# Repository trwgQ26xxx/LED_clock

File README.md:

# LED clock with thermometer

Clock with DS3231/DS3231M RTC.

# Disclaimer

I do not consent to the use of all or part of the project for commercial purposes!

Nie wyrażam zgody na wykorzystanie całości bądź części projektu w celach zarobkowych!

# License

Shield: [![CC BY-NC-SA 4.0][cc-by-nc-sa-shield]][cc-by-nc-sa]

This work is licensed under a
[Creative Commons Attribution-NonCommercial-ShareAlike 4.0 International License][cc-by-nc-sa].

[![CC BY-NC-SA 4.0][cc-by-nc-sa-image]][cc-by-nc-sa]

[cc-by-nc-sa]: http://creativecommons.org/licenses/by-nc-sa/4.0/
[cc-by-nc-sa-image]: https://licensebuttons.net/l/by-nc-sa/4.0/88x31.png
[cc-by-nc-sa-shield]: https://img.shields.io/badge/License-CC%20BY--NC--SA%204.0-lightgrey.svg

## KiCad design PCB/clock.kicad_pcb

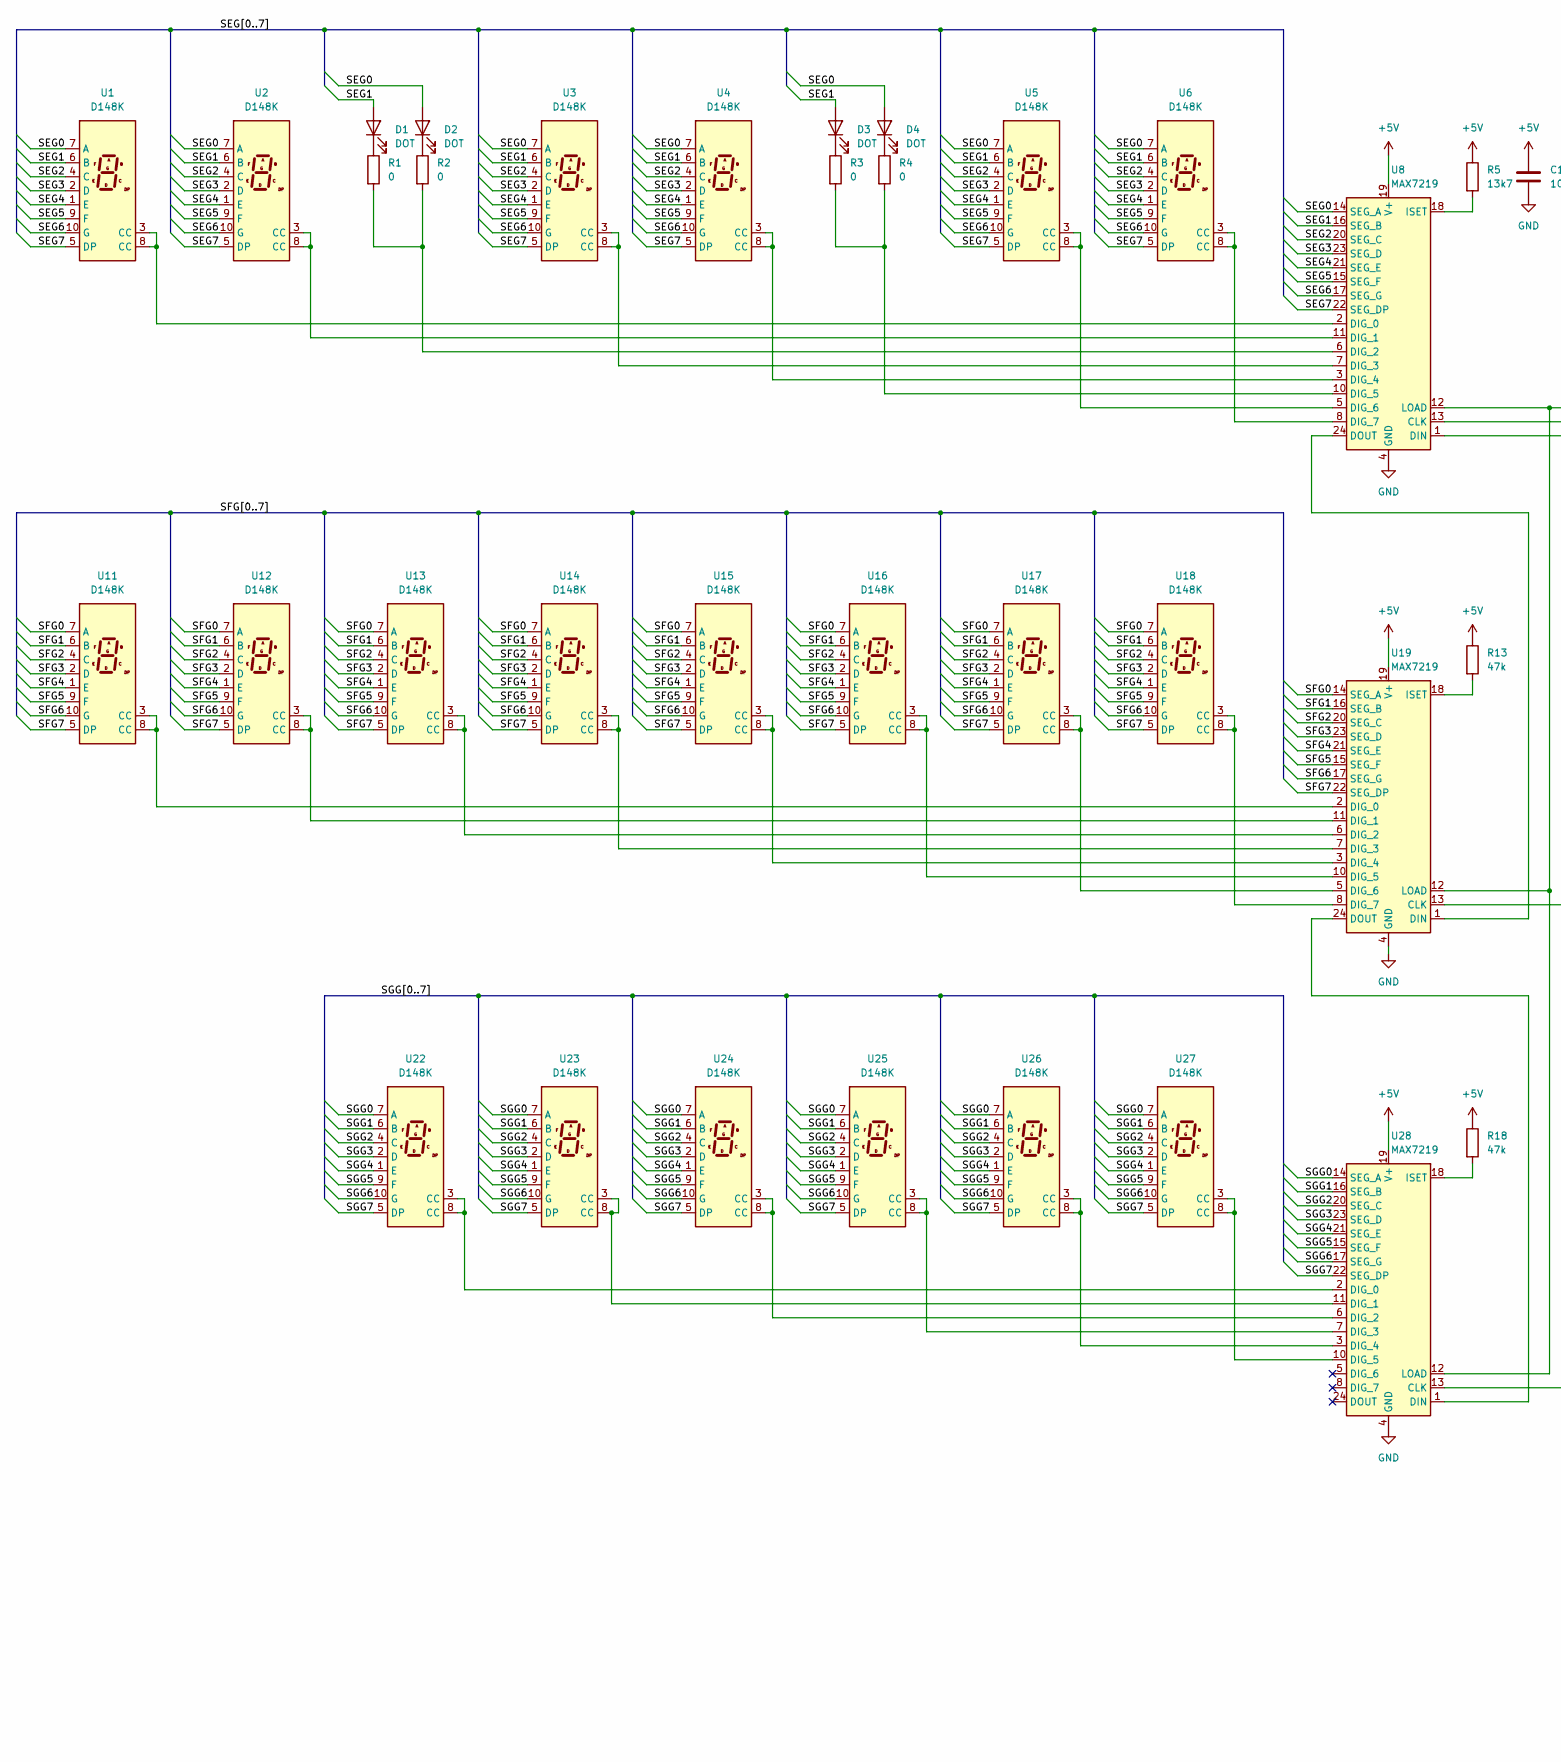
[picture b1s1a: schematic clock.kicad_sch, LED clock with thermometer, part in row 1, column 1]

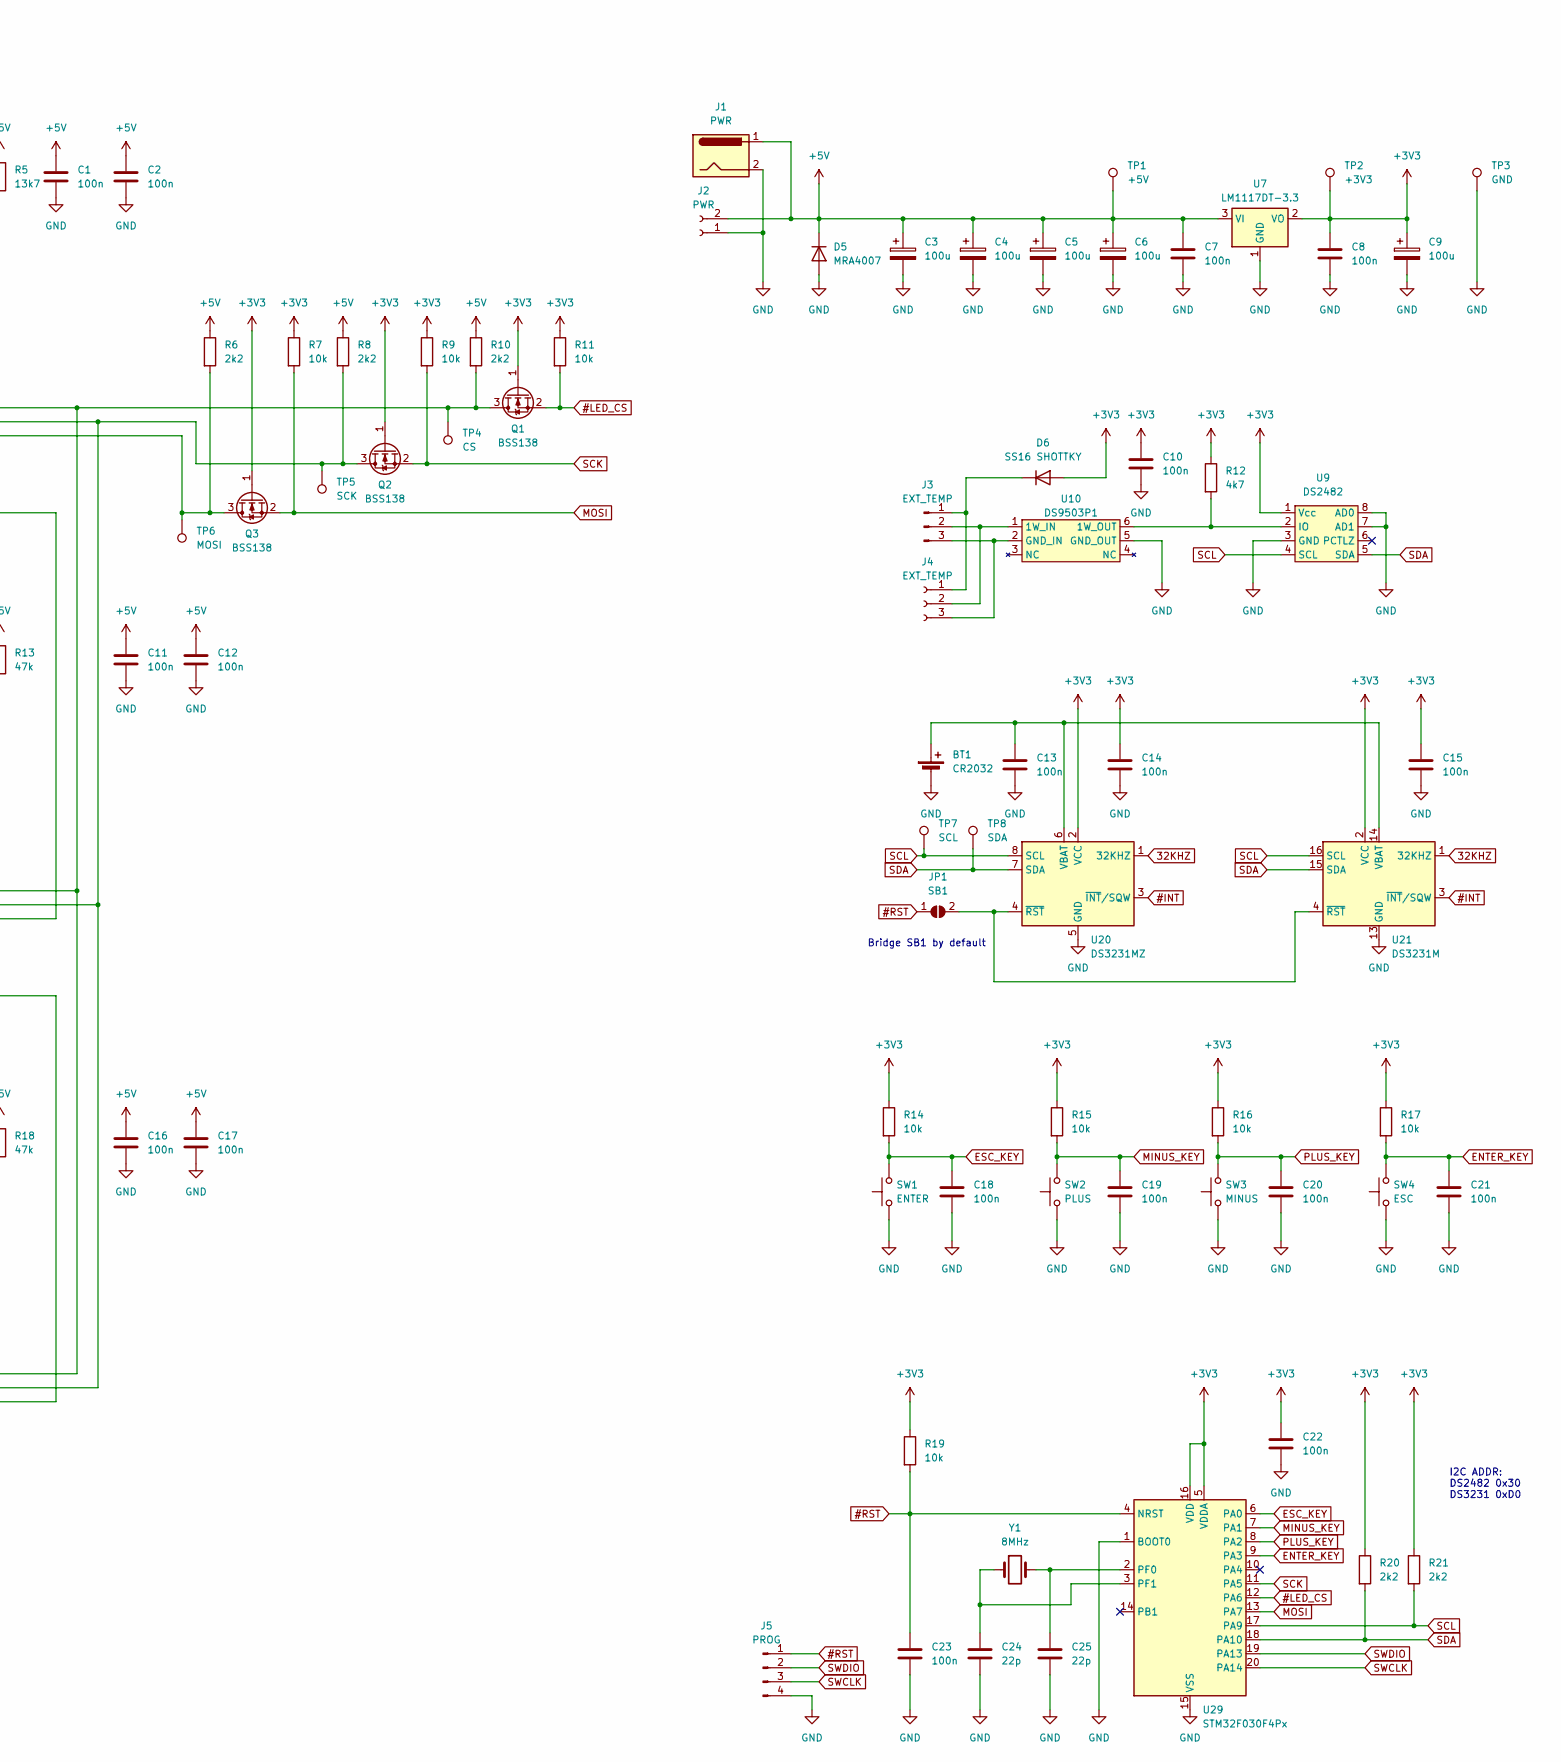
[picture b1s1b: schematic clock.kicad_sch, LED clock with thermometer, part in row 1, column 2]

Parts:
BT1: CR2032; Battery_Panasonic_CR2032-HFN_Horizontal_CircularHoles
C1, C2, C7, C8, C10, C11, C12, C13, C14, C15, C16, C17, C18, C19, C20, C21, C22, C23: 100n; C_1206_3216Metric_Pad1.33x1.80mm_HandSolder
C3, C4, C5, C6, C9: 100u; CP_Elec_8x6.5
C24, C25: 22p; C_1206_3216Metric_Pad1.33x1.80mm_HandSolder
D1, D2, D3, D4: DOT; LED_D5.0mm
D5: MRA4007; D_SMA
D6: SS16 SHOTTKY; D_SMA
J1: PWR; BarrelJack_Wuerth_6941xx301002
J2: PWR; TerminalBlock_bornier-2_P5.08mm
J3: EXT_TEMP; PinSocket_1x03_P2.54mm_Horizontal
J4: EXT_TEMP; TerminalBlock_bornier-3_P5.08mm
J5: PROG; PinSocket_1x04_P2.54mm_Horizontal
JP1: SB1; SolderJumper-2_P1.3mm_Open_RoundedPad1.0x1.5mm
Q1, Q2, Q3: BSS138; SOT-23
R1, R2, R3, R4: 0; R_1206_3216Metric_Pad1.30x1.75mm_HandSolder
R5: 13k7; R_1206_3216Metric_Pad1.30x1.75mm_HandSolder
R6, R8, R10, R20, R21: 2k2; R_1206_3216Metric_Pad1.30x1.75mm_HandSolder
R7, R9, R11, R14, R15, R16, R17, R19: 10k; R_1206_3216Metric_Pad1.30x1.75mm_HandSolder
R12: 4k7; R_1206_3216Metric_Pad1.30x1.75mm_HandSolder
R13, R18: 47k; R_1206_3216Metric_Pad1.30x1.75mm_HandSolder
SW1: ENTER; SW_PUSH-12mm_Wuerth-430476085716
SW2: PLUS; SW_PUSH-12mm_Wuerth-430476085716
SW3: MINUS; SW_PUSH-12mm_Wuerth-430476085716
SW4: ESC; SW_PUSH-12mm_Wuerth-430476085716
TP1: +5V; TestPoint_Pad_D2.0mm
TP2: +3V3; TestPoint_Pad_D2.0mm
TP3: GND; TestPoint_Pad_D2.0mm
TP4: CS; TestPoint_Pad_D2.0mm
TP5: SCK; TestPoint_Pad_D2.0mm
TP6: MOSI; TestPoint_Pad_D2.0mm
TP7: SCL; TestPoint_Pad_D2.0mm
TP8: SDA; TestPoint_Pad_D2.0mm
U1, U2, U3, U4, U5, U6: D148K; 0_8_INCH_LED
U7: LM1117DT-3.3; TO-252-3_TabPin2
U8, U19, U28: MAX7219; SOIC-24W_7.5x15.4mm_P1.27mm
U9: DS2482; SOIC-8_3.9x4.9mm_P1.27mm
U10: DS9503P1; TSOC-6_3.76x3.94mm_P1.27mm
U11, U12, U13, U14, U15, U16, U17, U18, U22, U23, U24, U25, U26, U27: D148K; Sx39-1xxxxx
U20: DS3231MZ; SOIC-8_3.9x4.9mm_P1.27mm
U21: DS3231M; SOIC-16W_7.5x10.3mm_P1.27mm
U29: STM32F030F4Px; TSSOP-20_4.4x6.5mm_P0.65mm
Y1: 8MHz; Crystal_SMD_HC49-SD_HandSoldering

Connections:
32KHZ: U20.1 (32KHZ), U21.1 (32KHZ)
#INT: U20.3 (~INT/SQW), U21.3 (~INT/SQW)
#LED_CS: Q1.2 (S), R11.2, U29.12 (PA6)
#RST: C23.1, J5.1, JP1.1 (A), R19.2, U29.4 (NRST)
+3V3: C8.1, C9.1, C10.1, C14.1, C15.1, C22.1, D6.2 (A), Q1.1 (G), Q2.1 (G), Q3.1 (G), R7.1, R9.1, R11.1, R12.1, R14.1, R15.1, R16.1, R17.1, R19.1, R20.1, R21.1, TP2.1, U7.2 (VO), U9.1 (Vcc), U20.2 (VCC), U21.2 (VCC), U29.5 (VDDA), U29.16 (VDD)
+5V: C1.1, C2.1, C3.1, C4.1, C5.1, C6.1, C7.1, C11.1, C12.1, C16.1, C17.1, D5.1 (K), J1.1, J2.2, R5.1, R6.1, R8.1, R10.1, R13.1, R18.1, TP1.1, U7.3 (VI), U8.19 (V+), U19.19 (V+), U28.19 (V+)
/SEG0: D2.2 (A), D4.2 (A), U1.7 (A), U2.7 (A), U3.7 (A), U4.7 (A), U5.7 (A), U6.7 (A), U8.14 (SEG_A)
/SEG1: D1.2 (A), D3.2 (A), U1.6 (B), U2.6 (B), U3.6 (B), U4.6 (B), U5.6 (B), U6.6 (B), U8.16 (SEG_B)
/SEG2: U1.4 (C), U2.4 (C), U3.4 (C), U4.4 (C), U5.4 (C), U6.4 (C), U8.20 (SEG_C)
/SEG3: U1.2 (D), U2.2 (D), U3.2 (D), U4.2 (D), U5.2 (D), U6.2 (D), U8.23 (SEG_D)
/SEG4: U1.1 (E), U2.1 (E), U3.1 (E), U4.1 (E), U5.1 (E), U6.1 (E), U8.21 (SEG_E)
/SEG5: U1.9 (F), U2.9 (F), U3.9 (F), U4.9 (F), U5.9 (F), U6.9 (F), U8.15 (SEG_F)
/SEG6: U1.10 (G), U2.10 (G), U3.10 (G), U4.10 (G), U5.10 (G), U6.10 (G), U8.17 (SEG_G)
/SEG7: U1.5 (DP), U2.5 (DP), U3.5 (DP), U4.5 (DP), U5.5 (DP), U6.5 (DP), U8.22 (SEG_DP)
/SFG0: U11.7 (A), U12.7 (A), U13.7 (A), U14.7 (A), U15.7 (A), U16.7 (A), U17.7 (A), U18.7 (A), U19.14 (SEG_A)
/SFG1: U11.6 (B), U12.6 (B), U13.6 (B), U14.6 (B), U15.6 (B), U16.6 (B), U17.6 (B), U18.6 (B), U19.16 (SEG_B)
/SFG2: U11.4 (C), U12.4 (C), U13.4 (C), U14.4 (C), U15.4 (C), U16.4 (C), U17.4 (C), U18.4 (C), U19.20 (SEG_C)
/SFG3: U11.2 (D), U12.2 (D), U13.2 (D), U14.2 (D), U15.2 (D), U16.2 (D), U17.2 (D), U18.2 (D), U19.23 (SEG_D)
/SFG4: U11.1 (E), U12.1 (E), U13.1 (E), U14.1 (E), U15.1 (E), U16.1 (E), U17.1 (E), U18.1 (E), U19.21 (SEG_E)
/SFG5: U11.9 (F), U12.9 (F), U13.9 (F), U14.9 (F), U15.9 (F), U16.9 (F), U17.9 (F), U18.9 (F), U19.15 (SEG_F)
/SFG6: U11.10 (G), U12.10 (G), U13.10 (G), U14.10 (G), U15.10 (G), U16.10 (G), U17.10 (G), U18.10 (G), U19.17 (SEG_G)
/SFG7: U11.5 (DP), U12.5 (DP), U13.5 (DP), U14.5 (DP), U15.5 (DP), U16.5 (DP), U17.5 (DP), U18.5 (DP), U19.22 (SEG_DP)
/SGG0: U22.7 (A), U23.7 (A), U24.7 (A), U25.7 (A), U26.7 (A), U27.7 (A), U28.14 (SEG_A)
/SGG1: U22.6 (B), U23.6 (B), U24.6 (B), U25.6 (B), U26.6 (B), U27.6 (B), U28.16 (SEG_B)
/SGG2: U22.4 (C), U23.4 (C), U24.4 (C), U25.4 (C), U26.4 (C), U27.4 (C), U28.20 (SEG_C)
/SGG3: U22.2 (D), U23.2 (D), U24.2 (D), U25.2 (D), U26.2 (D), U27.2 (D), U28.23 (SEG_D)
/SGG4: U22.1 (E), U23.1 (E), U24.1 (E), U25.1 (E), U26.1 (E), U27.1 (E), U28.21 (SEG_E)
/SGG5: U22.9 (F), U23.9 (F), U24.9 (F), U25.9 (F), U26.9 (F), U27.9 (F), U28.15 (SEG_F)
/SGG6: U22.10 (G), U23.10 (G), U24.10 (G), U25.10 (G), U26.10 (G), U27.10 (G), U28.17 (SEG_G)
/SGG7: U22.5 (DP), U23.5 (DP), U24.5 (DP), U25.5 (DP), U26.5 (DP), U27.5 (DP), U28.22 (SEG_DP)
ENTER_KEY: C21.1, R17.2, SW4.2, U29.9 (PA3)
ESC_KEY: C18.1, R14.2, SW1.2, U29.6 (PA0)
GND: BT1.2 (-), C1.2, C2.2, C3.2, C4.2, C5.2, C6.2, C7.2, C8.2, C9.2, C10.2, C11.2, C12.2, C13.2, C14.2, C15.2, C16.2, C17.2, C18.2, C19.2, C20.2, C21.2, C22.2, C23.2, C24.2, C25.2, D5.2 (A), J1.2, J2.1, J5.4, SW1.1, SW2.1, SW3.1, SW4.1, TP3.1, U7.1 (GND), U8.4 (GND), U8.9 (GND), U9.3 (GND), U9.7 (AD1), U9.8 (AD0), U10.5 (GND_OUT), U19.4 (GND), U19.9 (GND), U20.5 (GND), U21.5 (GND), U21.6 (GND), U21.7 (GND), U21.8 (GND), U21.9 (GND), U21.10 (GND), U21.11 (GND), U21.12 (GND), U21.13 (GND), U28.4 (GND), U28.9 (GND), U29.1 (BOOT0), U29.15 (VSS)
MINUS_KEY: C19.1, R15.2, SW2.2, U29.7 (PA1)
MOSI: Q3.2 (S), R7.2, U29.13 (PA7)
unnamed: BT1.1 (+), C13.1, U20.6 (VBAT), U21.14 (VBAT)
unnamed: D1.1 (K), R1.1
unnamed: D2.1 (K), R2.1
unnamed: D3.1 (K), R3.1
unnamed: D4.1 (K), R4.1
unnamed: D6.1 (K), J3.1, J4.1
unnamed: J3.2, J4.2, U10.1 (1W_IN)
unnamed: J3.3, J4.3, U10.2 (GND_IN)
unnamed: JP1.2 (B), U20.4 (~RST), U21.4 (~RST)
unnamed: Q1.3 (D), R10.2, TP4.1, U8.12 (LOAD), U19.12 (LOAD), U28.12 (LOAD)
unnamed: Q2.3 (D), R8.2, TP5.1, U8.13 (CLK), U19.13 (CLK), U28.13 (CLK)
unnamed: Q3.3 (D), R6.2, TP6.1, U8.1 (DIN)
unnamed: U1.3 (CC), U1.8 (CC), U8.2 (DIG_0)
unnamed: U2.3 (CC), U2.8 (CC), U8.11 (DIG_1)
unnamed: R1.2, R2.2, U8.6 (DIG_2)
unnamed: U3.3 (CC), U3.8 (CC), U8.7 (DIG_3)
unnamed: U4.3 (CC), U4.8 (CC), U8.3 (DIG_4)
unnamed: R3.2, R4.2, U8.10 (DIG_5)
unnamed: U5.3 (CC), U5.8 (CC), U8.5 (DIG_6)
unnamed: U6.3 (CC), U6.8 (CC), U8.8 (DIG_7)
unnamed: R5.2, U8.18 (ISET)
unnamed: R12.2, U9.2 (IO), U10.6 (1W_OUT)
unnamed: U11.3 (CC), U11.8 (CC), U19.2 (DIG_0)
unnamed: U12.3 (CC), U12.8 (CC), U19.11 (DIG_1)
unnamed: U13.3 (CC), U13.8 (CC), U19.6 (DIG_2)
unnamed: U14.3 (CC), U14.8 (CC), U19.7 (DIG_3)
unnamed: U15.3 (CC), U15.8 (CC), U19.3 (DIG_4)
unnamed: U16.3 (CC), U16.8 (CC), U19.10 (DIG_5)
unnamed: U17.3 (CC), U17.8 (CC), U19.5 (DIG_6)
unnamed: U18.3 (CC), U18.8 (CC), U19.8 (DIG_7)
unnamed: U8.24 (DOUT), U19.1 (DIN)
unnamed: U19.24 (DOUT), U28.1 (DIN)
unnamed: R13.2, U19.18 (ISET)
unnamed: U22.3 (CC), U22.8 (CC), U28.2 (DIG_0)
unnamed: U23.3 (CC), U23.8 (CC), U28.11 (DIG_1)
unnamed: U24.3 (CC), U24.8 (CC), U28.6 (DIG_2)
unnamed: U25.3 (CC), U25.8 (CC), U28.7 (DIG_3)
unnamed: U26.3 (CC), U26.8 (CC), U28.3 (DIG_4)
unnamed: U27.3 (CC), U27.8 (CC), U28.10 (DIG_5)
unnamed: R18.2, U28.18 (ISET)
unnamed: C25.1, U29.2 (PF0), Y1.2
unnamed: C24.1, U29.3 (PF1), Y1.1
PLUS_KEY: C20.1, R16.2, SW3.2, U29.8 (PA2)
SCK: Q2.2 (S), R9.2, U29.11 (PA5)
SCL: R21.2, TP7.1, U9.4 (SCL), U20.8 (SCL), U21.16 (SCL), U29.17 (PA9)
SDA: R20.2, TP8.1, U9.5 (SDA), U20.7 (SDA), U21.15 (SDA), U29.18 (PA10)
SWCLK: J5.3, U29.20 (PA14)
SWDIO: J5.2, U29.19 (PA13)

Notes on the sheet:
I2C ADDR: DS2482 0x30 DS3231 0xD0
Bridge SB1 by default

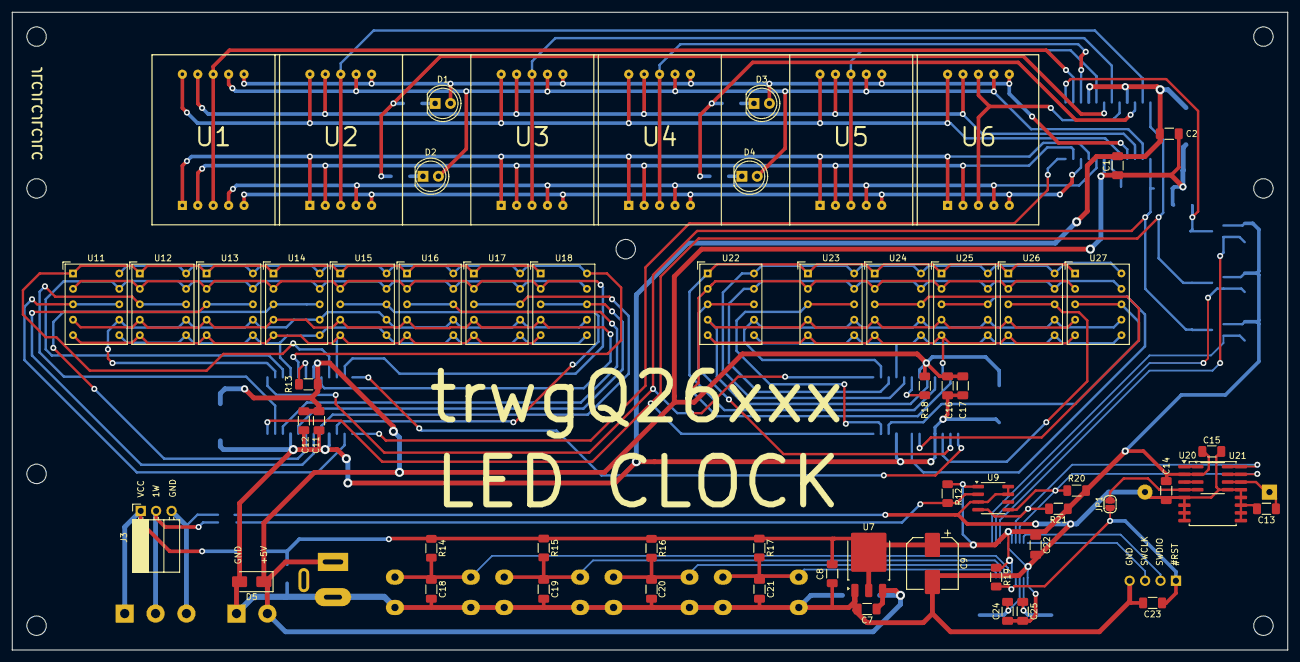
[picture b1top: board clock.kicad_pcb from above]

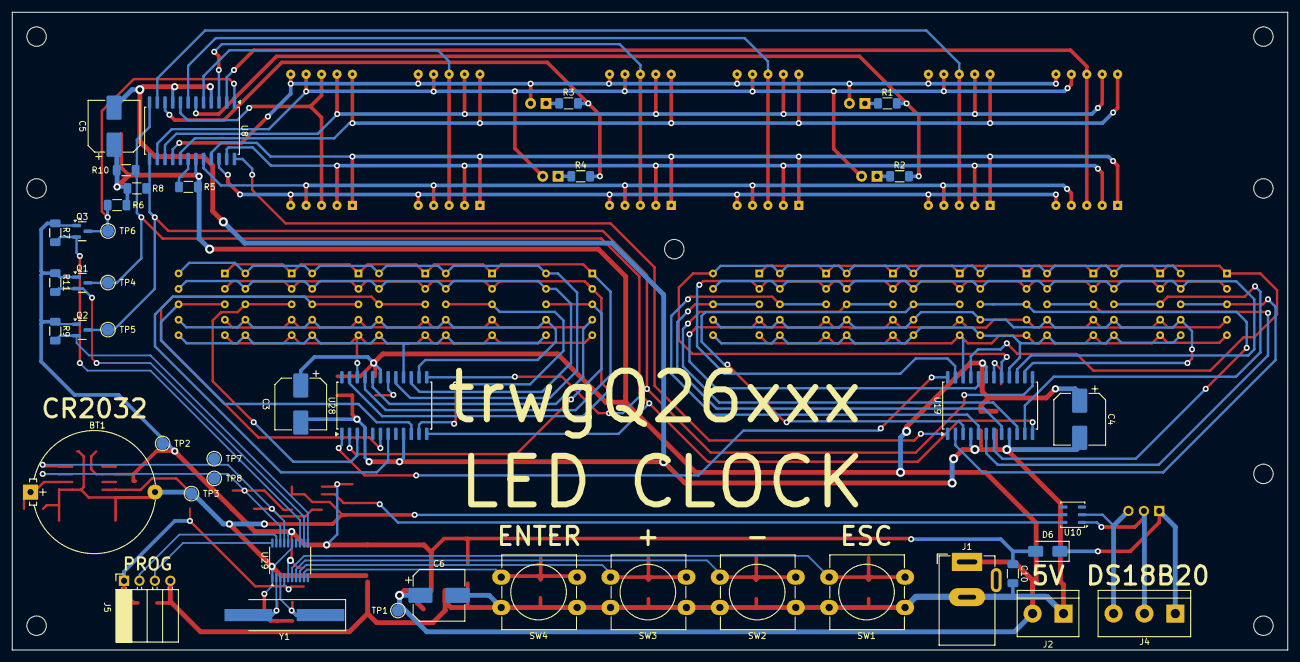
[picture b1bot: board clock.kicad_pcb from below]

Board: 2 copper layers, 210.0 x 105.0 mm, 104 parts (43 on the bottom side), 83 nets.

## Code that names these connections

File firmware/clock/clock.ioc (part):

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Mcu.Name=STM32F030F4Px
Mcu.Package=TSSOP20
Mcu.UserName=STM32F030F4Px
PA0.GPIOParameters=GPIO_PuPd,GPIO_Label
PA0.GPIO_Label=ESC_KEY
PA0.GPIO_PuPd=GPIO_PULLUP
PA0.Signal=GPIO_Input
PA1.GPIOParameters=GPIO_PuPd,GPIO_Label
PA1.GPIO_Label=MINUS_KEY
PA1.GPIO_PuPd=GPIO_PULLUP
PA1.Signal=GPIO_Input
PA10.Mode=I2C
PA10.Signal=I2C1_SDA
PA13.Mode=Serial_Wire
PA13.Signal=SYS_SWDIO
PA14.Mode=Serial_Wire
PA14.Signal=SYS_SWCLK
PA2.GPIOParameters=GPIO_PuPd,GPIO_Label
PA2.GPIO_Label=PLUS_KEY
PA2.GPIO_PuPd=GPIO_PULLUP
PA2.Signal=GPIO_Input
PA3.GPIOParameters=GPIO_PuPd,GPIO_Label
PA3.GPIO_Label=ENTER_KEY
PA3.GPIO_PuPd=GPIO_PULLUP
PA3.Signal=GPIO_Input
PA4.GPIOParameters=GPIO_PuPd,GPIO_Label
PA4.GPIO_Label=UNUSED_1
PA4.GPIO_PuPd=GPIO_PULLUP
PA4.Signal=GPIO_Input
PA5.Mode=TX_Only_Simplex_Unidirect_Master
PA5.Signal=SPI1_SCK
PA6.GPIOParameters=GPIO_Speed,PinState,GPIO_Label
PA6.GPIO_Label=LED_CS
PA6.GPIO_Speed=GPIO_SPEED_FREQ_HIGH
PA6.PinState=GPIO_PIN_SET
PA6.Signal=GPIO_Output
PA7.Mode=TX_Only_Simplex_Unidirect_Master
PA7.Signal=SPI1_MOSI
PA9.Mode=I2C
PA9.Signal=I2C1_SCL
PB1.GPIOParameters=GPIO_PuPd,GPIO_Label
PB1.GPIO_Label=UNUSED_2
PB1.GPIO_PuPd=GPIO_PULLUP
PB1.Signal=GPIO_Input
PF0-OSC_IN.Mode=HSE-External-Oscillator
PF0-OSC_IN.Signal=RCC_OSC_IN
PF1-OSC_OUT.Mode=HSE-External-Oscillator
PF1-OSC_OUT.Signal=RCC_OSC_OUT
RCC.HSE_Timout=100
RCC.SYSCLKFreq_VALUE=16000000
RCC.SYSCLKSource=RCC_SYSCLKSOURCE_PLLCLK
board=custom

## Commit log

2024-09-16 Full PCB project added
2025-02-08 Basic firmware implemented
2025-02-08 License added
2025-02-08 Minor update
2025-02-09 STM F0 packs updated from V1.11.4 to V1.11.5
2025-02-09 TMR14 configured to update display 10 times per second, SPI reconfigured for 125kHz
2025-02-09 WDT configured for 100ms
2025-02-09 Implemented basic storing LED intensity in FLASH
2025-02-09 Added intensity display
2025-02-09 Updated gitignore
2025-02-09 PCB updated with final component values
2025-02-12 SYSCLK reconfigured for 16MHz PLL, as it is more stable than using the HSE directly
2025-02-12 SPI reconfigured for more robust configuration
2025-02-12 Update to more robust implementation
2025-02-13 RTC & display update are synchronized now. LED update split to two phases for lower latency
2025-02-13 Intensity display moved from temperature display to date display
2025-02-13 Implemented quit to normal mode if no buttons are pressed for 10s in set mode
2025-02-13 Refactor
2025-02-15 Logic shifter resistors readjustment
2025-02-16 Hardware CRC configured
2025-02-16 Flash driver updated, settings are CRC protected now
2025-02-16 Minor readjustments
2025-02-16 RTC driver reworked
2025-02-16 Timeout for setting time changed from 10s to 60s
2025-02-16 IWDG enable moved to last step
2025-02-19 Reworked I2C, part 1
2025-02-24 I2C driver reworked
2025-02-24 RTC data update only is performed now only if RTC read was successful
2025-02-25 Added basic clock photo
2025-03-01 Disable keyboard to prevent selecting options if any key would be stuck at startup
2025-10-15 Added LED displays KiCad libraries
2025-10-15 Datasheets added
2025-10-15 Added update synchronization method sheet
2025-10-18 Added sticker and mounting plate to repository
2025-10-25 External temperature sensor (DS18B20) implemented
2025-10-25 Datasheets added, sync sheet updated
